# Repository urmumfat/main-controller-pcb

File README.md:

# pg-id-656-main-controller-pcb
Custom PCB for an autonomous wheeled robot

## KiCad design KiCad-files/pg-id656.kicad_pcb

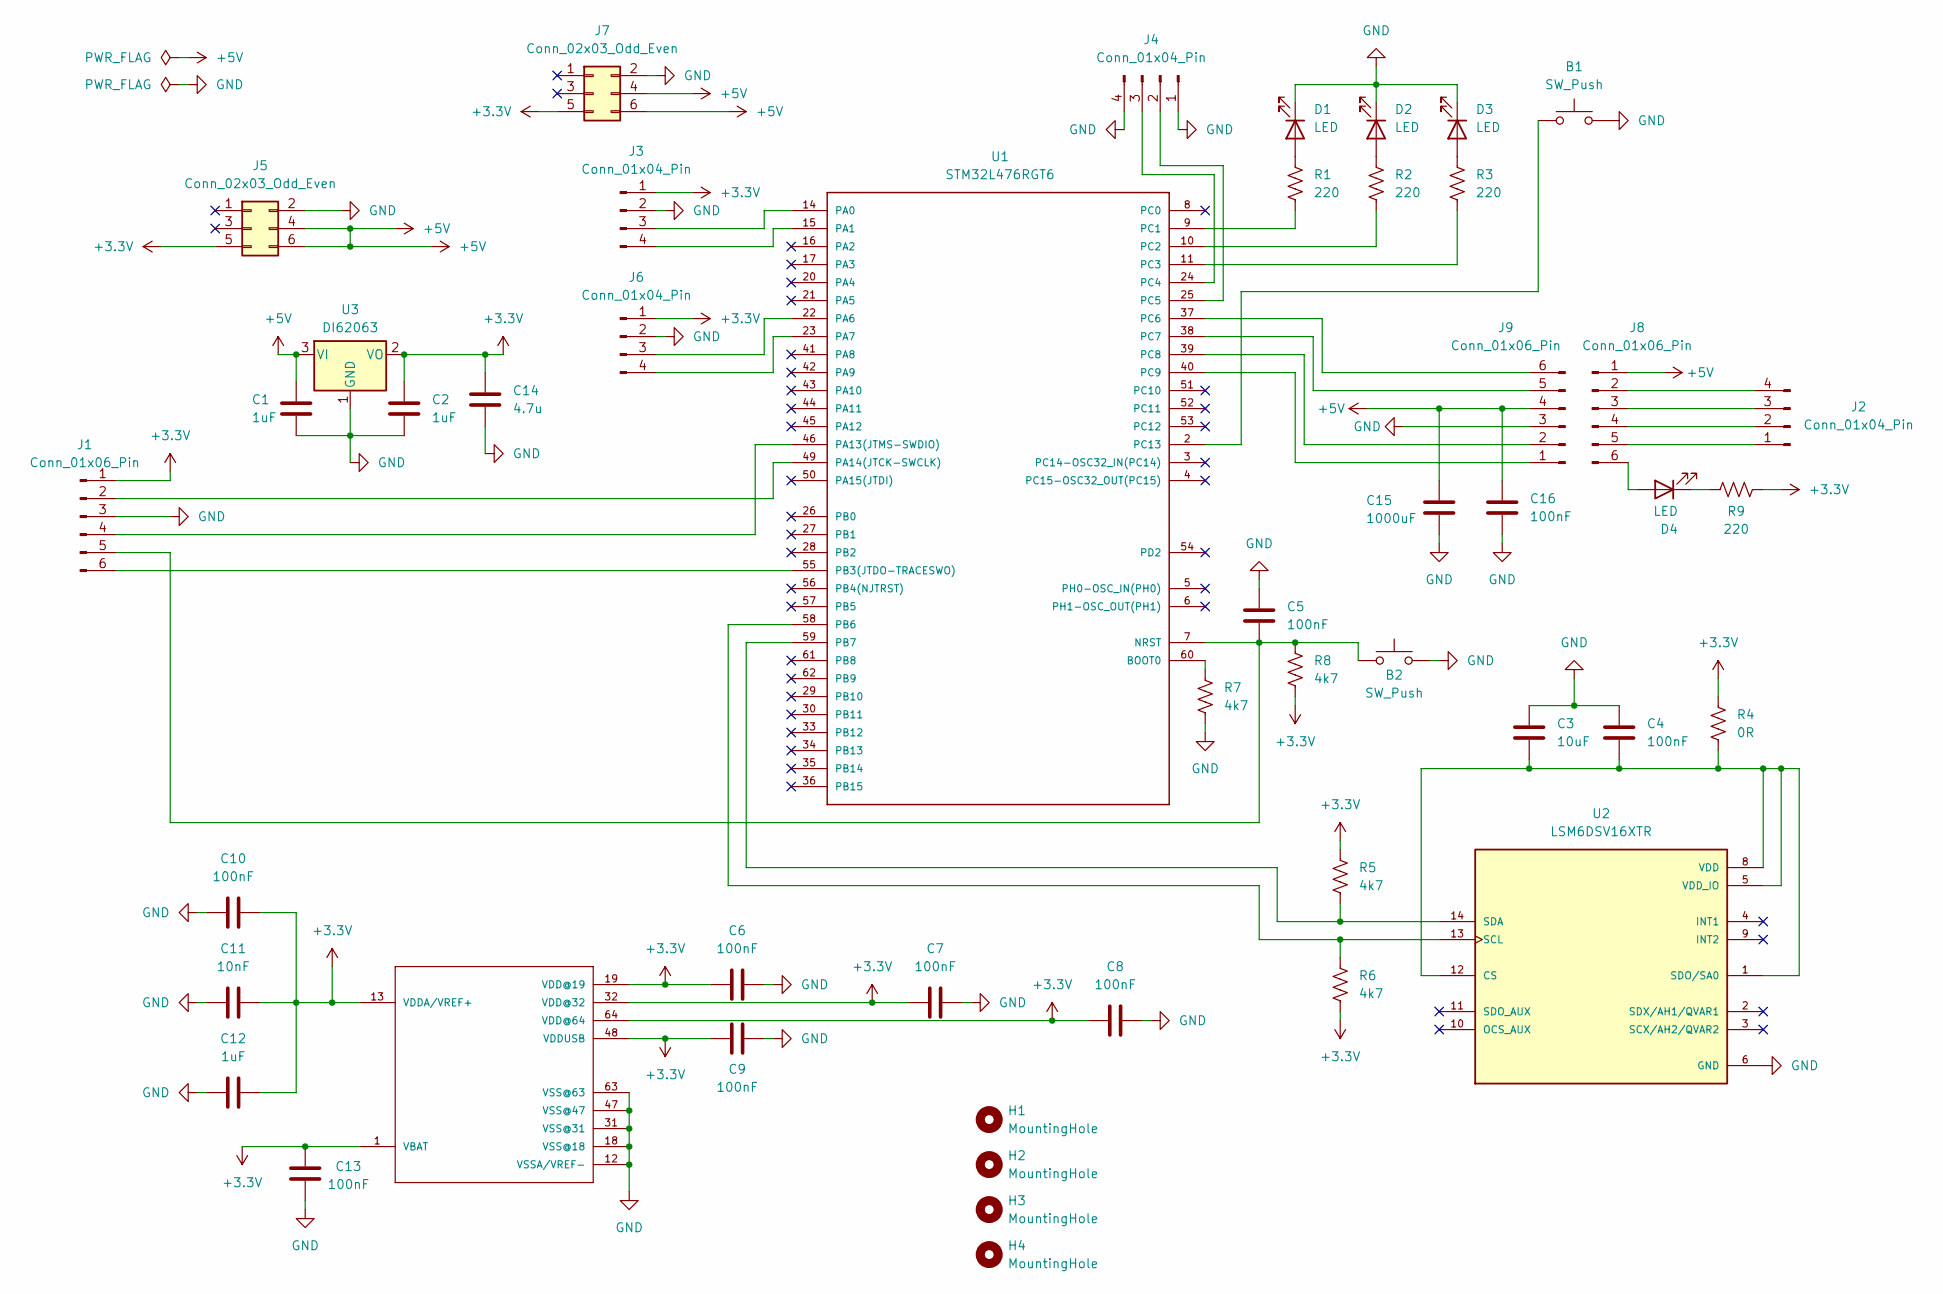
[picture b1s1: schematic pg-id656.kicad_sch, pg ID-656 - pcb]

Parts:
B1, B2: SW_Push; SW_PUSH_6mm
C1, C2, C12: 1uF; C_0805_2012Metric
C3: 10uF; C_0805_2012Metric
C4, C5, C6, C7, C8, C9, C10, C13, C16: 100nF; C_0603_1608Metric
C11: 10nF; C_0603_1608Metric
C14: 4.7u; C_0603_1608Metric
C15: 1000uF; CP_Elec_8x10
D1, D2, D3, D4: LED; LED_0603_1608Metric
H1, H2, H3, H4: MountingHole; MountingHole_3.2mm_M3_DIN965
J1, J8, J9: Conn_01x06_Pin; PinHeader_1x06_P2.54mm_Vertical
J2, J3, J4, J6: Conn_01x04_Pin; PinHeader_1x04_P2.54mm_Vertical
J5, J7: Conn_02x03_Odd_Even; PinHeader_2x03_P2.54mm_Vertical
R1, R2, R3, R9: 220; R_0603_1608Metric
R4: 0R; R_0805_2012Metric
R5, R6, R7, R8: 4k7; R_0603_1608Metric
U1: STM32L476RGT6; LQFP-64_10X10_MM
U2: LSM6DSV16XTR; XDCR_LSM6DSV16XTR; PARTREV 4
U3: DI62063; SOT-23

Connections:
+3.3V: C2.2, C6.1, C7.1, C8.1, C9.2, C10.2, C11.2, C12.2, C13.2, C14.2, J1.1, J3.1, J5.5, J6.1, J7.5, R4.1, R5.1, R6.2, R8.2, R9.1, U1.1 (VBAT), U1.13 (VDDA/VREF+), U1.19 (VDD@19), U1.32 (VDD@32), U1.48 (VDDUSB), U1.64 (VDD@64), U3.2 (VO)
+5V: C1.2, C15.2, C16.2, J5.4, J5.6, J7.4, J7.6, J8.1, J9.4, U3.3 (VI)
GND: B1.2, B2.2, C1.1, C2.1, C3.1, C4.1, C5.1, C6.2, C7.2, C8.2, C9.1, C10.1, C11.1, C12.1, C13.1, C14.1, C15.1, C16.1, D1.1 (K), D2.1 (K), D3.1 (K), J1.3, J3.2, J4.1, J4.4, J5.2, J6.2, J7.2, J9.3, R7.2, U1.12 (VSSA/VREF-), U1.18 (VSS@18), U1.31 (VSS@31), U1.47 (VSS@47), U1.63 (VSS@63), U2.6 (GND), U2.7 (GND), U3.1 (GND); also elsewhere on the board
unnamed: D1.2 (A), R1.1
unnamed: D2.2 (A), R2.1
unnamed: D3.2 (A), R3.1
unnamed: D4.2 (A), J8.6
unnamed: D4.1 (K), R9.2
unnamed: J1.2, U1.49 (PA14(JTCK-SWCLK))
unnamed: J1.4, U1.46 (PA13(JTMS-SWDIO))
unnamed 10: B2.1, C5.2, J1.5, R8.1, U1.7 (NRST); also elsewhere on the board
unnamed: J1.6, U1.55 (PB3(JTDO-TRACESWO))
unnamed: J2.1, J8.5
unnamed: J2.2, J8.4
unnamed: J2.3, J8.3
unnamed: J2.4, J8.2
unnamed: J3.3, U1.14 (PA0)
unnamed: J3.4, U1.15 (PA1)
unnamed: J4.2, U1.25 (PC5)
unnamed: J4.3, U1.24 (PC4)
unnamed: J6.3, U1.22 (PA6)
unnamed: J6.4, U1.23 (PA7)
unnamed: J9.1, U1.40 (PC9)
unnamed: J9.2, U1.39 (PC8)
unnamed: J9.5, U1.38 (PC7)
unnamed: J9.6, U1.37 (PC6)
unnamed: R7.1, U1.60 (BOOT0)
unnamed 27: R6.1, U1.58 (PB6), U2.13 (SCL); also elsewhere on the board
unnamed 28: R5.2, U1.59 (PB7), U2.14 (SDA); also elsewhere on the board
unnamed: R1.2, U1.9 (PC1)
unnamed: R2.2, U1.10 (PC2)
unnamed: R3.2, U1.11 (PC3)
unnamed: B1.1, U1.2 (PC13)
unnamed 33: C3.2, C4.2, R4.2, U2.1 (SDO/SA0), U2.5 (VDD_IO), U2.8 (VDD), U2.12 (CS); also elsewhere on the board

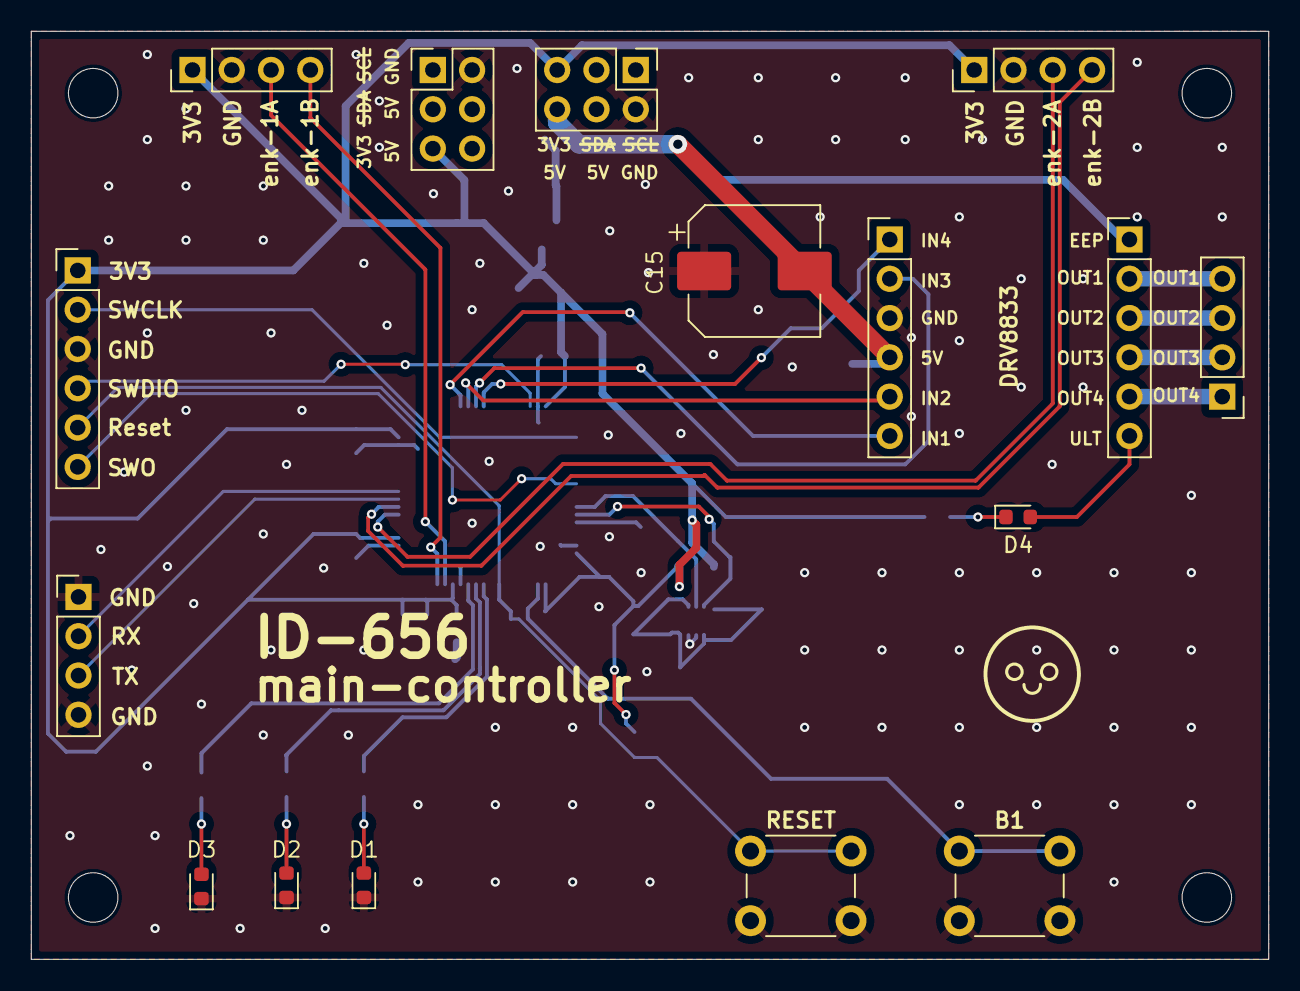
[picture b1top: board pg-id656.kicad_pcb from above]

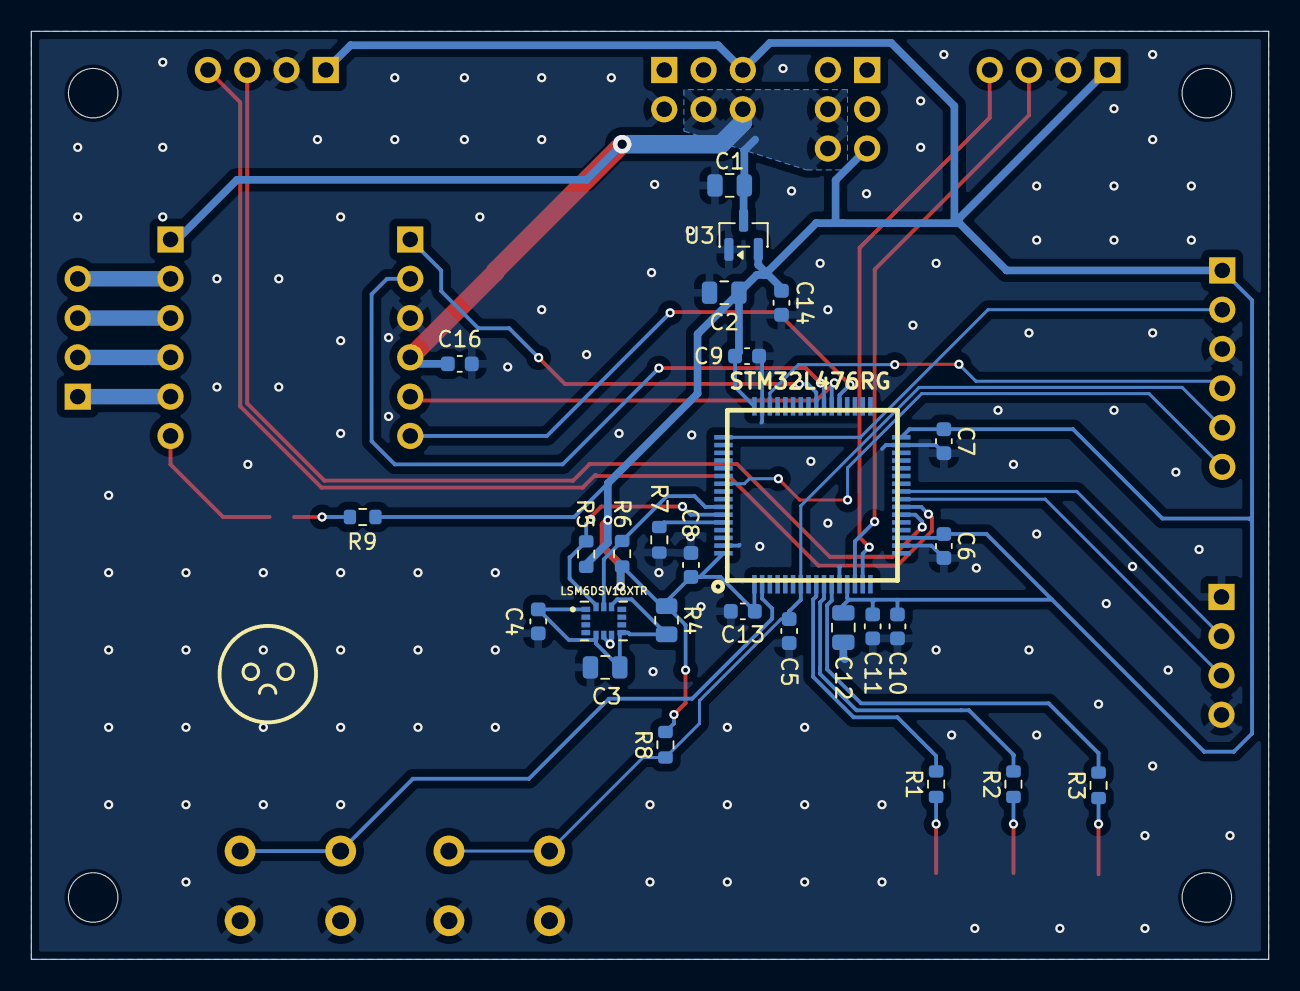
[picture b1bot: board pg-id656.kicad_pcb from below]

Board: 2 copper layers, 80.0 x 60.0 mm, 47 parts (27 on the bottom side), 34 nets.

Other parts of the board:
LSM6DSV16XTR: LSM6DSV16XTR; XDCR_LSM6DSV16XTR
RESET: SW_Push; SW_PUSH_6mm

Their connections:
GND: LSM6DSV16XTR.6 (GND), LSM6DSV16XTR.7 (GND), RESET.2; also elsewhere on the board
unnamed 10: RESET.1; also elsewhere on the board
unnamed 27: LSM6DSV16XTR.13 (SCL); also elsewhere on the board
unnamed 28: LSM6DSV16XTR.14 (SDA); also elsewhere on the board
unnamed 33: LSM6DSV16XTR.1 (SDO/SA0), LSM6DSV16XTR.5 (VDD_IO), LSM6DSV16XTR.8 (VDD), LSM6DSV16XTR.12 (CS); also elsewhere on the board

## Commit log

2026-04-07 schematics_v1 upload
2026-04-08 schematics v2
2026-04-08 schematics v3
2026-04-09 schematics v4
2026-04-09 schematics v5
2026-04-09 pcb v1
2026-04-09 pcb v2
2026-04-10 pcb v3
2026-04-10 schematics v6-final
2026-04-15 schematics v7
2026-04-20 pcb v4
2026-04-22 pcb v5
2026-04-22 schematics v8
2026-04-24 pcb v6
2026-04-24 pcb v7
2026-04-24 pcb v8
2026-04-24 added gerber files
2026-04-24 added KiCad files
2026-04-24 added licence
2026-04-24 licence revision
2026-04-28 added 3D models
